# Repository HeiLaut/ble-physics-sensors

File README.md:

# BLE Sensors for physics class

* [Goal](#goal)
* [Microcontroller and Sensors](#sensors)
   * [Force Sensor](#force)
   * [ToF Distance-Sensor](#tof)
   * [Light Gate](#gate)
   * [Magnetometer](#magnet)
   * [DC Multimeter](#multimeter)
   * [Barometer](#barometer) 

## Goal 

**Easy to use** and affordable sensor boxes for digital data acquisition are suitable for use in physics lessons by students or for teacher demonstrations.

Each box can be assembled for less than 20 €.

Comments and requests for changes to both the 3D files and the Arduino code are welcome.

## Microcontroller and Sensors 

All boxes are equipped with an ESP32, enabling them to communicate via BLE (Bluetooth Low Energy) or a serial connection.

I use the Wemos Lolin32Lite development board because of its availability, the battery connector and the low price.

Most sensors use the I2C interface to communicate with the ESP32.

### Force Sensor 

Sensor:

Load Cell and HX711 amplifier

### ToF Distance-Sensor 

Sensor:

VL53L0X

or

VL53L1X

[Assembly instructions see wiki](https://github.com/HeiLaut/ble-physics-sensors/wiki/Laser-Distance)

### Light Gate 

Sensor:

Adafruit Break Beam Sensor 

or (cheaper)

modified lightgate/speed-sensor with LM393

### Magnetometer 

Sensor:

LIS2MDL

or

MLX90393

or

(Gy-271) low range 

### DC Multimeter 

Sensor:

INA219

and (optional)

ADS1115

Example Videos:

Diode characteristic https://youtu.be/DQ5L0hsJfBA

Resistor characteristic https://youtu.be/PSxBtcULFwU

Charge and discharge of a capacitor https://youtube.com/shorts/HkM0g7PQ94s?feature=share

### Barometer 

BMP180 Barometer and Thermometer module.

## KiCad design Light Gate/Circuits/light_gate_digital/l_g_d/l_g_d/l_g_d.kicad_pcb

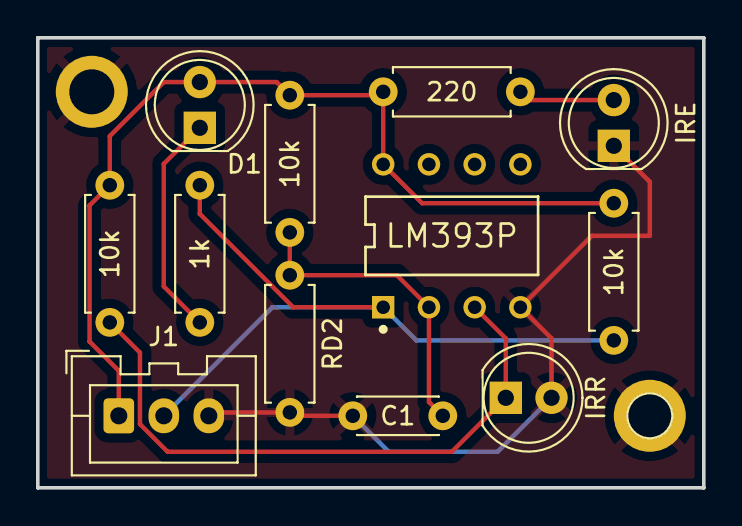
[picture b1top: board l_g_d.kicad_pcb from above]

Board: 2 copper layers, 37.0 x 25.0 mm, 12 parts (0 on the bottom side), 7 nets.

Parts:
1k: 1k; R_Axial_DIN0207_L6.3mm_D2.5mm_P7.62mm_Horizontal
10k, 10k#2, 10k#3: 10k; R_Axial_DIN0207_L6.3mm_D2.5mm_P7.62mm_Horizontal
220: 220; R_Axial_DIN0207_L6.3mm_D2.5mm_P7.62mm_Horizontal
C1: C; C_Disc_D4.3mm_W1.9mm_P5.00mm
D1: LED; LED_D5.0mm_IRGrey
IRE: LD271; LED_D5.0mm_IRGrey
IRR: Q_Photo_NPN_CE; LED_D5.0mm_IRGrey
J1: Conn_01x03_Female; JST_XA_B03B-XASK-1_1x03_P2.50mm_Vertical
RD2: 10k; R_Axial_DIN0207_L6.3mm_D2.5mm_P7.62mm_Horizontal
U1: LM393P; Texas_Instruments-P_R-PDIP-T8-0-0-0

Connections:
GND: C1.1, IRE.1 (K), IRR.2 (E), J1.3, RD2.2, U1.4 (GND)
unnamed: 10k.2, C1.2, RD2.1, U1.2 (1IN−)
unnamed: 1k.1, D1.1 (K)
unnamed: 220.2, IRE.2 (A)
unnamed: 1k.2, 10k#2.2, J1.2, U1.1 (1OUT)
unnamed: 10k#3.1, IRR.1 (C), U1.3 (1IN+)
VCC: 10k.1, 10k#2.1, 10k#3.2, 220.1, D1.2 (A), J1.1, U1.8 (VCC)

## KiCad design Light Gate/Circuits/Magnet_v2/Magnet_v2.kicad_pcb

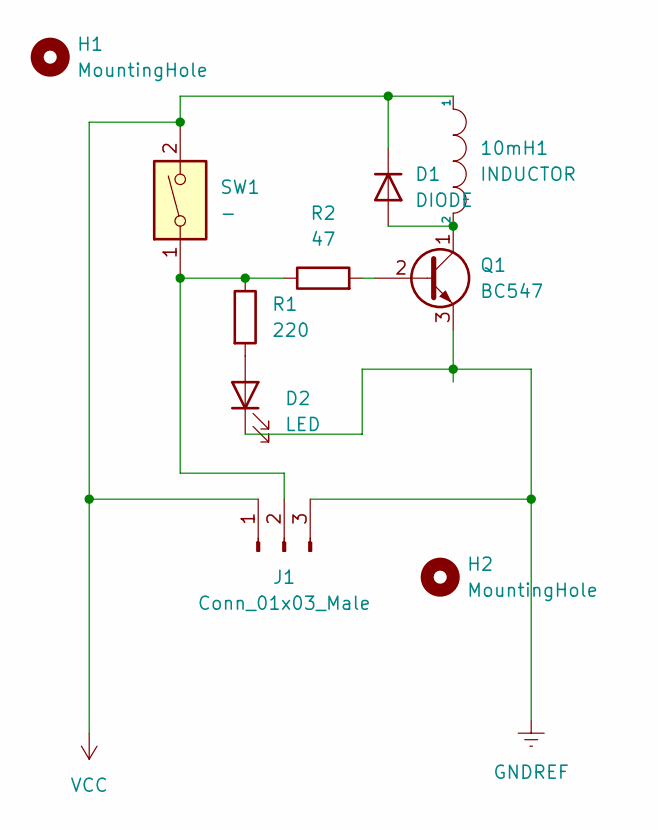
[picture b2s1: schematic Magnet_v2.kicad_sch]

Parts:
10mH1: INDUCTOR; PinSocket_1x02_P2.54mm_Vertical
D1: DIODE; D_T-1_P10.16mm_Horizontal
D2: LED; LED_D5.0mm
H1, H2: MountingHole; MountingHole_2.5mm
J1: Conn_01x03_Male; PinSocket_1x03_P2.54mm_Vertical
Q1: BC547; TO-92_HandSolder
R1: 220; R_Axial_DIN0207_L6.3mm_D2.5mm_P7.62mm_Horizontal
R2: 47; R_Axial_DIN0207_L6.3mm_D2.5mm_P7.62mm_Horizontal
SW1: -; PinSocket_1x02_P2.54mm_Vertical

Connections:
GNDREF: D2.1 (K), J1.3, Q1.3 (E)
unnamed: 10mH1.2, D1.1 (A), Q1.1 (C)
unnamed: D2.2 (A), R1.2
unnamed: J1.2, R1.1, R2.1, SW1.1
unnamed: Q1.2 (B), R2.2
VCC: 10mH1.1, D1.2 (K), J1.1, SW1.2

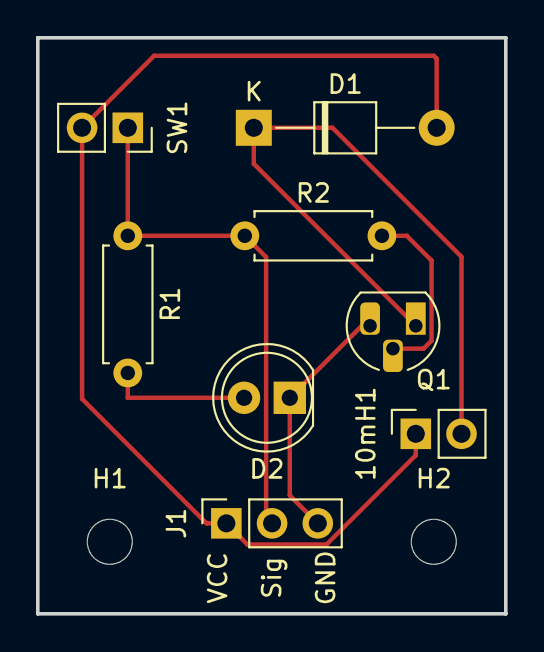
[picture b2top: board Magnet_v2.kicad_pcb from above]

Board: 2 copper layers, 26.0 x 32.0 mm, 10 parts (0 on the bottom side), 6 nets.

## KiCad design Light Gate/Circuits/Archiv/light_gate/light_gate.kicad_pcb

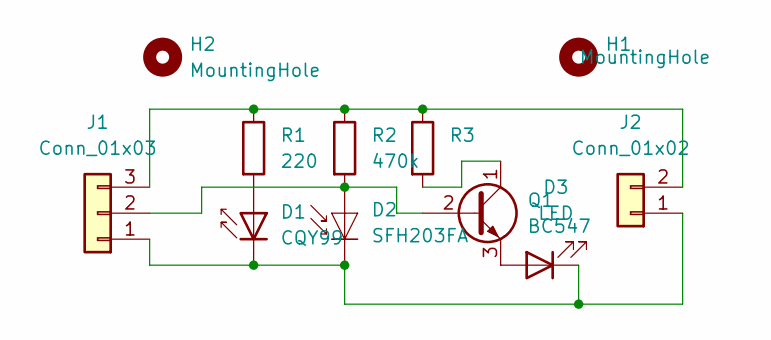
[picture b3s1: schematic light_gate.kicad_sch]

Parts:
D1: CQY99; LED_D5.0mm_IRGrey
D2: SFH203FA; LED_D5.0mm_IRGrey
D3: LED; LED_D5.0mm
H1, H2: MountingHole; MountingHole_2.2mm_M2_DIN965
J1: Conn_01x03; PinHeader_1x03_P2.54mm_Vertical
J2: Conn_01x02; PinHeader_1x02_P2.54mm_Vertical
Q1: BC547; TO-92L_HandSolder
R1: 220; R_Axial_DIN0207_L6.3mm_D2.5mm_P7.62mm_Horizontal
R2: 470k; R_Axial_DIN0207_L6.3mm_D2.5mm_P7.62mm_Horizontal
R3: R_Axial_DIN0207_L6.3mm_D2.5mm_P7.62mm_Horizontal

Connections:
unnamed: D1.1 (K), D2.1 (K), D3.1 (K), J1.1, J2.1
unnamed: D1.2 (A), R1.2
unnamed: D2.2 (A), J1.2, Q1.2 (B), R2.2
unnamed: D3.2 (A), Q1.3 (E)
unnamed: J1.3, J2.2, R1.1, R2.1, R3.1
unnamed: Q1.1 (C), R3.2

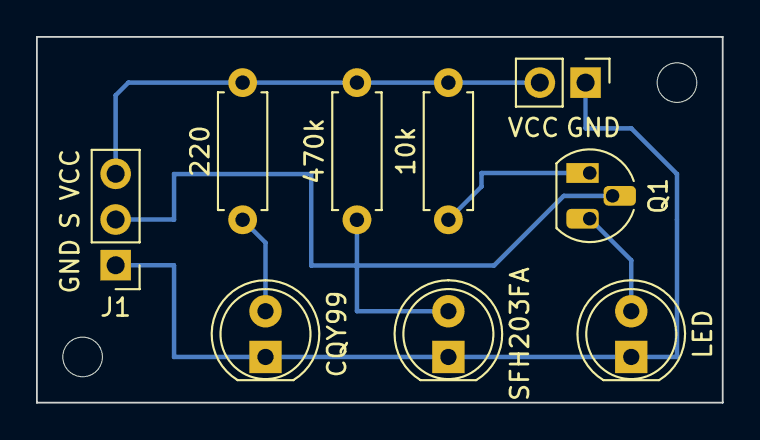
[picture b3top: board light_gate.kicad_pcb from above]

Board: 2 copper layers, 38.1 x 20.3 mm, 11 parts (0 on the bottom side), 6 nets.

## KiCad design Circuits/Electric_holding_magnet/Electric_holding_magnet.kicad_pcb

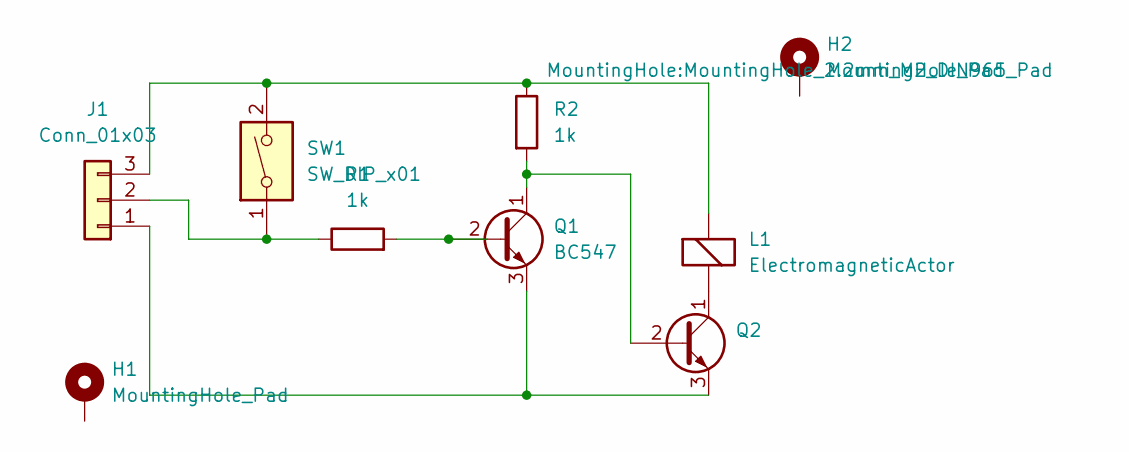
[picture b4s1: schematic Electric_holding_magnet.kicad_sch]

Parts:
H1, H2: MountingHole_Pad; MountingHole_2.2mm_M2_DIN965_Pad
J1: Conn_01x03; PinHeader_1x03_P2.54mm_Vertical
L1: ElectromagneticActor; PinHeader_1x02_P2.54mm_Vertical
Q1: BC547
Q2: (no value)
R1, R2: 1k; R_Axial_DIN0207_L6.3mm_D2.5mm_P7.62mm_Horizontal
SW1: SW_DIP_x01; PinHeader_1x02_P2.54mm_Vertical

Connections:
unnamed 0: J1.1, Q1.3 (E), Q2.3 (E); also elsewhere on the board
unnamed 1: J1.2, R1.1, SW1.1; also elsewhere on the board
unnamed: J1.3, L1.1 (-), R2.1, SW1.2
unnamed: L1.2 (+), Q2.1 (C)
unnamed: Q1.1 (C), Q2.2 (B), R2.2
unnamed: Q1.2 (B), R1.2

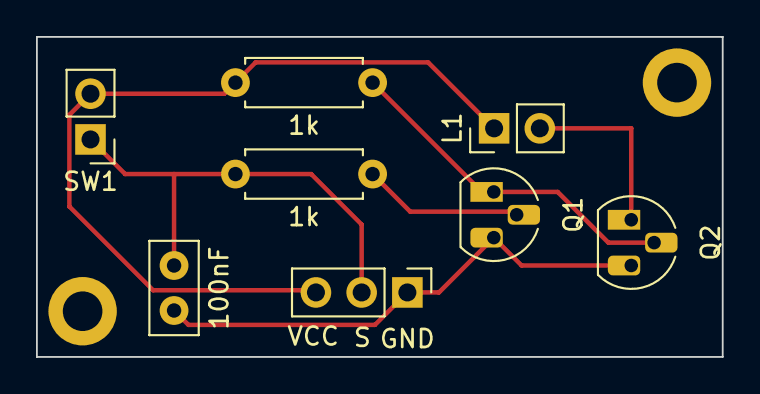
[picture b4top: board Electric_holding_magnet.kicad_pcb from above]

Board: 2 copper layers, 38.1 x 17.8 mm, 10 parts (0 on the bottom side), 6 nets.

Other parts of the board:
100nF: C; C_Disc_D5.0mm_W2.5mm_P2.50mm

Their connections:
unnamed 0: 100nF.2; also elsewhere on the board
unnamed 1: 100nF.1; also elsewhere on the board

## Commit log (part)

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2022-03-04 Create Plotter_v2.1.py
    addes file
2022-03-04 add files
2022-03-04 added discription
2022-03-04 added space for esp32 d1 in lid
2022-03-04 change port
2022-03-04 edit sensor description
2022-03-04 edit Title
2022-03-05 changed tolerances in load cell hull
2022-03-05 add sleep so no double values appear
2022-03-05 Update Load_Cell_Hull.scad
    changed lid
2022-03-06 added tare button
2022-03-07 redesign load_cell_hull
2022-03-08 tuning hull
2022-03-08 work on stl
2022-03-09 finalize hull for force
2022-03-09 added photos, tweak ino for force
2022-03-09 edit lid
2022-03-10 added ultrasonic and voltmeter files
2022-03-10 updatet mount for ultrasonic sensor box
2022-03-10 added circuits
2022-03-11 add english version
2022-03-11 change serial rate
2022-03-11 esp32 voltmeter
    changed to work with esp32
2022-03-11 added name of the serial plotter
2022-03-12 changed velocity and added multiple phyphox views
2022-03-12 Update us_distancemeter.ino
    chenged labelnames
2022-03-14 added images
2022-03-14 add images
2022-03-14 add us_example phyphox
2022-03-14 changed 3dp file
2022-03-15 ToF laser
    Added ToF-Laser 3dp files and first ino
2022-03-15 changed tof tolerances
2022-03-16 added phyphox support
2022-03-16 changed button hole
2022-03-16 add phtoto
2022-03-16 changed folder and name
2022-03-17 changed views
    add velocity to view and add adjustable delay
2022-03-17 added circuit
2022-03-17 changed fritzing
2022-03-17 added editable delay
2022-03-18 changed lid
    now lid can be screwed
2022-03-18 spelling
2022-03-18 changed lid parameters
2022-03-21 removed unused library
2022-03-21 changed to new lid design
2022-03-21 changed images
2022-03-23 added scale function
    added a third view, which shows the mass of the object.
    changed Precision of the forcemeasurement
2022-03-24 created voltmeter box for esp32
2022-03-24 change ino to measure correct voltage
2022-03-29 added views
2022-03-29 added first sketch
2022-03-29 added time differences
2022-03-31 add phyphox add second channel
    second channel not implemented in phyphox yet
2022-03-31 added files
    added files for the light barrier and the case for the esp32 - same as the voltmeter case
2022-03-31 updated case
2022-04-02 dual channel light barrier
2022-04-03 changed clearance
2022-04-03 simplyfied the file
2022-04-04 changed to 6 channels
2022-04-07 new serial handling
2022-04-07 createt case for magnet starter
2022-04-07 created new case with esp
2022-04-19 added case with din
2022-04-19 added kicad files
2022-04-21 add dc Multimeter
2022-04-21 added lght gate
2022-04-21 added circuit for ina219
2022-04-21 added multimter print files
2022-04-21 added arduino code
2022-04-21 added new version of case
2022-04-28 removed stl files
2022-04-28 removed files, not needed
2022-04-28 removed files not needed
2022-04-28 udated footprints npn
2022-04-28 changed pin
2022-04-28 updated files
2022-04-30 update pnp footprint
2022-04-30 moved plotter.py
2022-04-30 added new Serial Plotter
2022-05-01 added multiple axis options
2022-05-02 fixed small bugs
2022-05-02 moved to other repository
2022-05-02 changed output for webseiralplotter
2022-05-13 added file
2022-05-13 added capacitor
2022-05-13 changed delay
2022-05-20 changed velocity
    the velocity is now calculated dynamicly
2022-05-20 added lolin 32 case
2022-05-20 added power to phyphox
2022-05-20 removed external sensor
2022-05-20 added case files
2022-06-21 activate i2c ports for lolin lite
2022-09-04 new file for lolin32
2022-09-04 new lolin case files
2022-09-04 changed pins and calfactor for use with lolin
2022-09-04 removed,
2022-09-06 correct wiring
2022-09-07 added second sensor
2022-10-05 changed case
2022-10-05 changed circuit
2022-10-05 added thermosensor
2022-10-05 created file with em digital em senosr board
2022-11-17 added lm393 to lightgate
2023-01-21 added simple r-speed-sensor
2023-01-21 small design changes
2023-01-21 added complete new case
2023-03-05 added files
2023-03-05 changed pins
2023-03-07 added lb case
2023-03-07 added ina and ads
2023-03-07 added
2023-04-20 Change the folder structure
2023-04-20 changed folder names
2024-01-10 Create tof_distance_lolin_wo_array.ino
    removed quickstats library and arrays, because it caused problems with the lolin lite usb-c board
2024-01-10 changed name
2024-01-29 changed folder for arduino
2024-01-29 updated code for use of a single light barrier
2024-01-29 new case
    added files for a completely new case design, moved old design in sepreate folder
2024-01-29 moved old files to archive
2024-02-17 removed
2024-02-17 optimized code for single light gate
2024-02-17 changed precision
2024-02-17 add case2 library file
2024-02-17 reorgenized files
2024-02-17 changed labelname
2024-02-25 added simple version for single light barrier
2024-02-25 reorganized files
2024-02-28 updatet light gate and messwagen 3dp files
2024-03-17 new sensor
    added new arduino sketch fpr mlx90393
    added case files for the sensor
    add readme for the case files
    created stl files
2024-03-17 bluedot_case
    added bluedot case files
2024-03-17 changed a lot
2024-03-20 case update
    complete update of the case. moved the old files in the archive
2024-03-20 minor changes
2024-03-25 Update README.md
    Remonde outdated Wiki Adel Sensors
2024-03-25 removed outdated pictures
2024-03-25 comment code
2024-03-25 add pictures
2024-03-25 add screenshots
2024-03-25 Update README.md
    added photos
2024-03-25 pictures
2024-03-29 Aktualisieren von README.md
2024-04-03 add usb-c variant
2024-04-06 added multigraph
2024-04-07 updated mounting possibilities
2024-04-07 moved files to archiv
2024-04-08 moved to athciv
2024-04-08 re arrange
    moved old to archiv, add new fil
2024-04-08 changed resistor
2024-04-08 changed screwtype
2024-04-08 add fritzing files
2024-06-11 file order
2024-06-11 deleted dublicates
2024-06-11 added constant for interrupts
2024-06-16 change to rising signal
2024-08-13 update case and code
2024-08-15 udpate wiring and remove old files
2024-09-07 update case
2024-09-15 sense start/stop/sync events in phyphox
2024-09-15 update force sensor case
2024-09-30 upload files
2024-09-30 update cases and sketches
2024-09-30 moved pichtures
2024-10-01 Rename Laser Distance Sensor/Externe_Sensoren_für_PhyPhox-1.pdf to Laser Distance Sensor/workbook/Gedämpfte Schwingung.pdf
2024-10-01 Rename Gedämpfte Schwingung.pdf to damped oscillation.pdf
2024-10-01 Rename damped oscillation.pdf to damped oscillation.pdf
2024-10-01 Rename Externe_Sensoren_für_PhyPhox-2.pdf to Arbeitsblatt - gedämpfte Schwingung.pdf
2024-10-08 new Sensor
2024-10-08 update wiring diagram
2024-10-08 update case with embossing
2024-10-14 temperature measure change
    added temperature sensor and change colors of graphs.
2024-10-14 add space for temperaturesensor
2025-01-11 add instruction pictures
2025-01-13 add buildplate light gate
2025-03-17 added switch position indicator
2025-03-17 update several parts and intro text
2025-03-18 sorting
    update licence and minor adjustments to the files
2025-03-21 Update magnetometer.ino
    added i2c adress to work with adafruit sensor
2025-03-21 added pin names
2025-08-21 update oled
2025-08-23 update to usb-c
2025-08-23 reorganize stl files,
    made the side panel ready for usb-C, cut the load_connector to fit properly in the case.
2025-08-29 add parts for stromwaage
2025-08-29 add constant SENSOR_NAME
2025-09-02 edit case
    added modified bottom part for smaller load cell
2025-09-02 calibration
2025-09-18 changed button case layout
2025-09-18 sync
2025-09-18 Eink readded
2025-10-23 changed
2025-10-23 add font
2025-11-22 optimzied code
2025-12-19 ino and scad updates
2026-03-27 added ema_filter
2026-06-07 cleanup old files
2026-06-18 added case for seperate emitter and receiver
